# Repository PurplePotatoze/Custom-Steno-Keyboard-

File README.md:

#  Steno Keyboard
I'm making my very own Steno Keyboard!! (In a nutshell, its a keyboard that you can type over 200 wpm because of the placement of the keys). 42 Keys, USB-C, with a Raspberry Pi Pico. Thank you Hackclub Stardance for funding this!

BOM:
- 1x Raspberry Pi Pico 2
- 10x M3x5mm Screws
- 10x M3 (3mm) Heatset inserts
- 42x Gateron Low Profile Switches
- 42x Gateron Low Profile Keycaps
- 1x 0.91 OLED (Pin order: GND-VCC-SCL-SDA)
- 1x PCB
- 2x 3D Printed Case
- 1x 1.4 M3 Spacers

Features:
- USB-C
- 42 Reprogrammable Keycaps
- Compatibility with Plover
- 0.91 Oled for status

# CAD

Very simple case, just 10 heat set inserts

# Schematics

42 SW Push in a matrix (12x4) with a 4 pin connector for the oled.

# PCB

Designed in Kicad, gets yours at JLCPCB or PCBway with my Gerber files.

# Firmware

KMK, very simple python based code. Firmware in "Production" file, flash onto Pico. Very modifiable. Also install Plover for the Steno.

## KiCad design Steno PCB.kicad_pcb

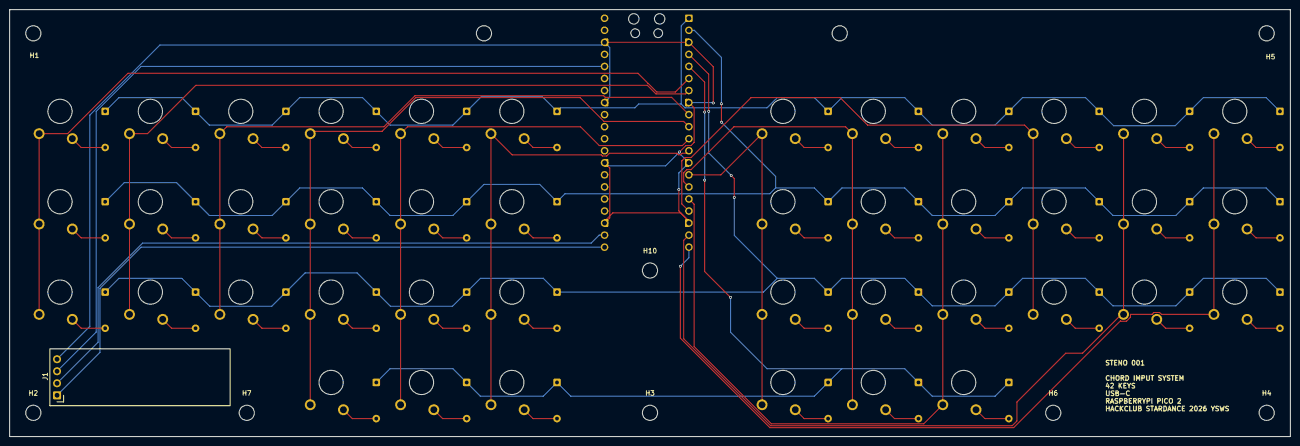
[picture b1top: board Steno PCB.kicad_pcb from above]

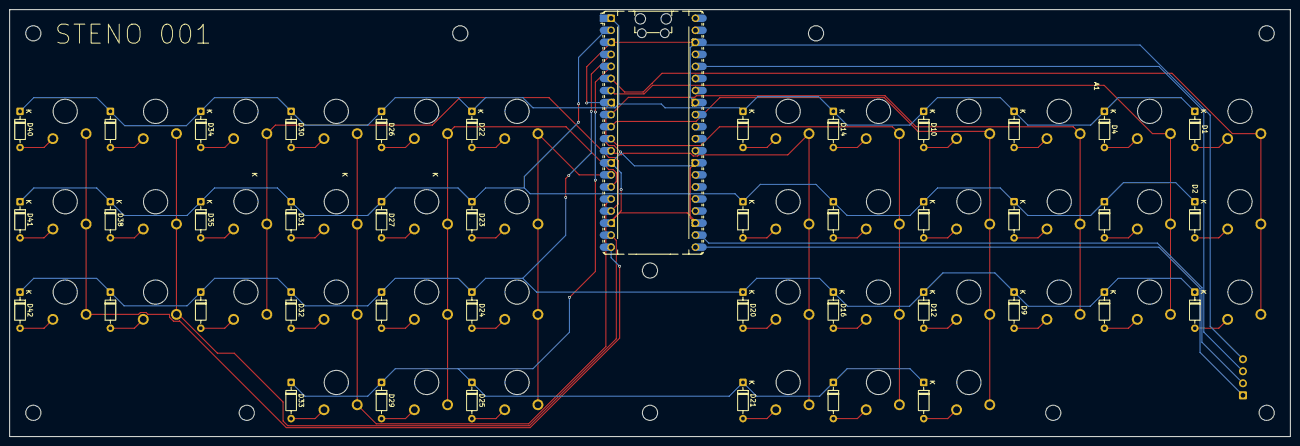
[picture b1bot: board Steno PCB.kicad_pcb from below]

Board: 2 copper layers, 270.0 x 90.0 mm, 96 parts (43 on the bottom side), 62 nets.

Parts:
A1: RaspberryPi_Pico; RaspberryPi_Pico_Common_Unspecified
D1, D2, D3, D4, D5, D6, D7, D8, D9, D10, D11, D12, D13, D14, D15, D16, D17, D18, D19, D20, D21, D22, D23, D24, D25, D26, D27, D28, D29, D30, D31, D32, D33, D34, D35, D36, D37, D38, D39, D40, D41, D42: 1N4148; D_DO-35_SOD27_P7.62mm_Horizontal
H1, H2, H3, H4, H5, H6, H7, H8, H9, H10: MountingHole; MountingHole_3.2mm_M3
J1: Conn_01x04_Pin; ER_OLEDM0.91_1x-I2C
SW1, SW2, SW3, SW4, SW5, SW6, SW7, SW8, SW9, SW10, SW11, SW12, SW13, SW14, SW15, SW16, SW17, SW18, SW19, SW20, SW21, SW22, SW23, SW24, SW25, SW26, SW27, SW28, SW29, SW30, SW31, SW32, SW33, SW34, SW35, SW36, SW37, SW38, SW39, SW40, SW41, SW42: SW_Push; Gateron-KS33-Solderable-1U

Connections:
+3.3V: A1.36 (3V3), J1.3
/ Column 1: A1.7 (GPIO5), SW4.1, SW5.1, SW6.1
/ Column 10: A1.19 (GPIO14), SW37.1, SW38.1, SW39.1
/Column 0: A1.6 (GPIO4), SW1.1, SW2.1, SW3.1
/Column 2: A1.9 (GPIO6), SW7.1, SW8.1, SW9.1
/Column 3: A1.10 (GPIO7), SW10.1, SW11.1, SW12.1, SW13.1
/Column 4: A1.11 (GPIO8), SW14.1, SW15.1, SW16.1, SW17.1
/Column 5: A1.12 (GPIO9), SW18.1, SW19.1, SW20.1, SW21.1
/Column 6: A1.14 (GPIO10), SW22.1, SW23.1, SW24.1, SW25.1
/Column 7: A1.15 (GPIO11), SW26.1, SW27.1, SW28.1, SW29.1
/Column 8: A1.16 (GPIO12), SW30.1, SW31.1, SW32.1, SW33.1
/Column 9: A1.17 (GPIO13), SW34.1, SW35.1, SW36.1
/Column 11: A1.20 (GPIO15), SW40.1, SW41.1, SW42.1
/Row 0: A1.1 (GPIO0), D1.1 (K), D4.1 (K), D7.1 (K), D10.1 (K), D14.1 (K), D18.1 (K), D22.1 (K), D26.1 (K), D30.1 (K), D34.1 (K), D37.1 (K), D40.1 (K)
/Row 1: A1.2 (GPIO1), D2.1 (K), D5.1 (K), D8.1 (K), D11.1 (K), D15.1 (K), D19.1 (K), D23.1 (K), D27.1 (K), D31.1 (K), D35.1 (K), D38.1 (K), D41.1 (K)
/Row 2: A1.4 (GPIO2), D3.1 (K), D6.1 (K), D9.1 (K), D12.1 (K), D16.1 (K), D20.1 (K), D24.1 (K), D28.1 (K), D32.1 (K), D36.1 (K), D39.1 (K), D42.1 (K)
/Row 3: A1.5 (GPIO3), D13.1 (K), D17.1 (K), D21.1 (K), D25.1 (K), D29.1 (K), D33.1 (K)
/SCL: A1.22 (GPIO17), J1.2
/SDA: A1.21 (GPIO16), J1.1
GND: A1.3 (GND), A1.8 (GND), A1.13 (GND), A1.18 (GND), A1.23 (GND), A1.28 (GND), A1.33 (AGND), A1.38 (GND), J1.4
unnamed: D1.2 (A), SW1.2
unnamed: D2.2 (A), SW2.2
unnamed: D3.2 (A), SW3.2
unnamed: D4.2 (A), SW4.2
unnamed: D5.2 (A), SW5.2
unnamed: D6.2 (A), SW6.2
unnamed: D7.2 (A), SW7.2
unnamed: D8.2 (A), SW8.2
unnamed: D9.2 (A), SW9.2
unnamed: D10.2 (A), SW10.2
unnamed: D11.2 (A), SW11.2
unnamed: D12.2 (A), SW12.2
unnamed: D13.2 (A), SW13.2
unnamed: D14.2 (A), SW14.2
unnamed: D15.2 (A), SW15.2
unnamed: D16.2 (A), SW16.2
unnamed: D17.2 (A), SW17.2
unnamed: D18.2 (A), SW18.2
unnamed: D19.2 (A), SW19.2
unnamed: D20.2 (A), SW20.2
unnamed: D21.2 (A), SW21.2
unnamed: D22.2 (A), SW22.2
unnamed: D23.2 (A), SW23.2
unnamed: D24.2 (A), SW24.2
unnamed: D25.2 (A), SW25.2
unnamed: D26.2 (A), SW26.2
unnamed: D27.2 (A), SW27.2
unnamed: D28.2 (A), SW28.2
unnamed: D29.2 (A), SW29.2
unnamed: D30.2 (A), SW30.2
unnamed: D31.2 (A), SW31.2
unnamed: D32.2 (A), SW32.2
unnamed: D33.2 (A), SW33.2
unnamed: D34.2 (A), SW34.2
unnamed: D35.2 (A), SW35.2
unnamed: D36.2 (A), SW36.2
unnamed: D37.2 (A), SW37.2
unnamed: D38.2 (A), SW38.2
unnamed: D39.2 (A), SW39.2
unnamed: D40.2 (A), SW40.2
unnamed: D41.2 (A), SW41.2
unnamed: D42.2 (A), SW42.2
